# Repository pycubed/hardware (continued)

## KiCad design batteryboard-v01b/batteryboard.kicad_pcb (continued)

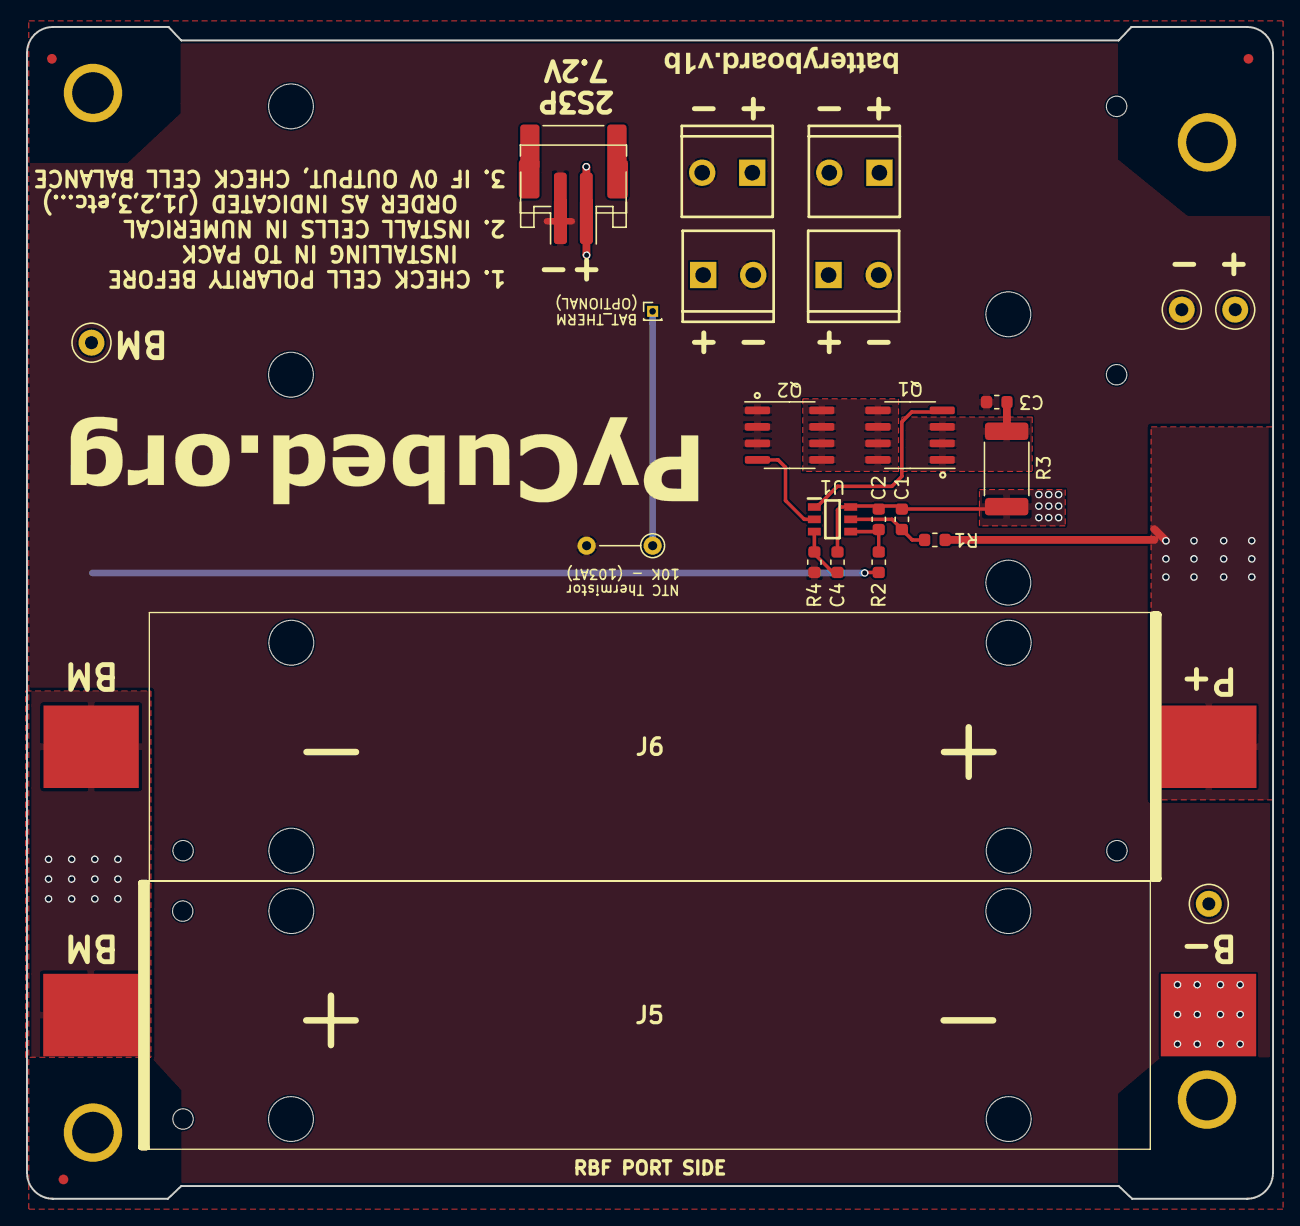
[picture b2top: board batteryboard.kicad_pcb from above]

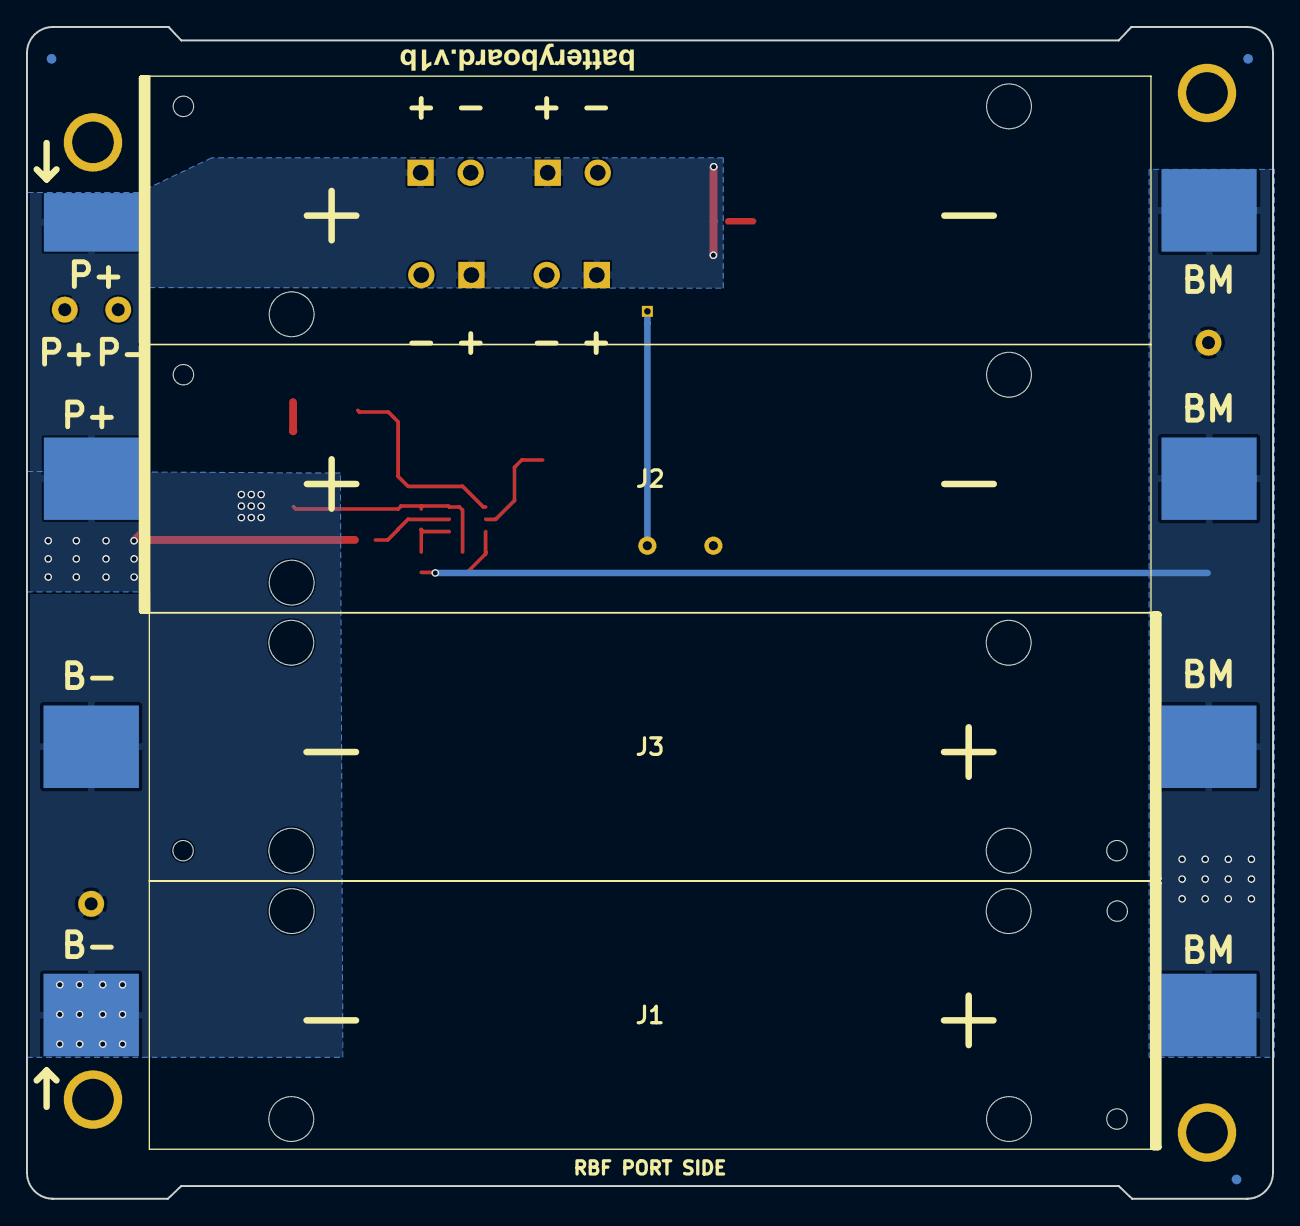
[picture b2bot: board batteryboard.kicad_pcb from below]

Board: 2 copper layers, 95.9 x 90.2 mm, 35 parts (5 on the bottom side), 12 nets.

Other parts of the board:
Ref**: Val**; battery_version
Ref**#2: Val**; battery_version
Ref**#3: Val**; pycubed_logo

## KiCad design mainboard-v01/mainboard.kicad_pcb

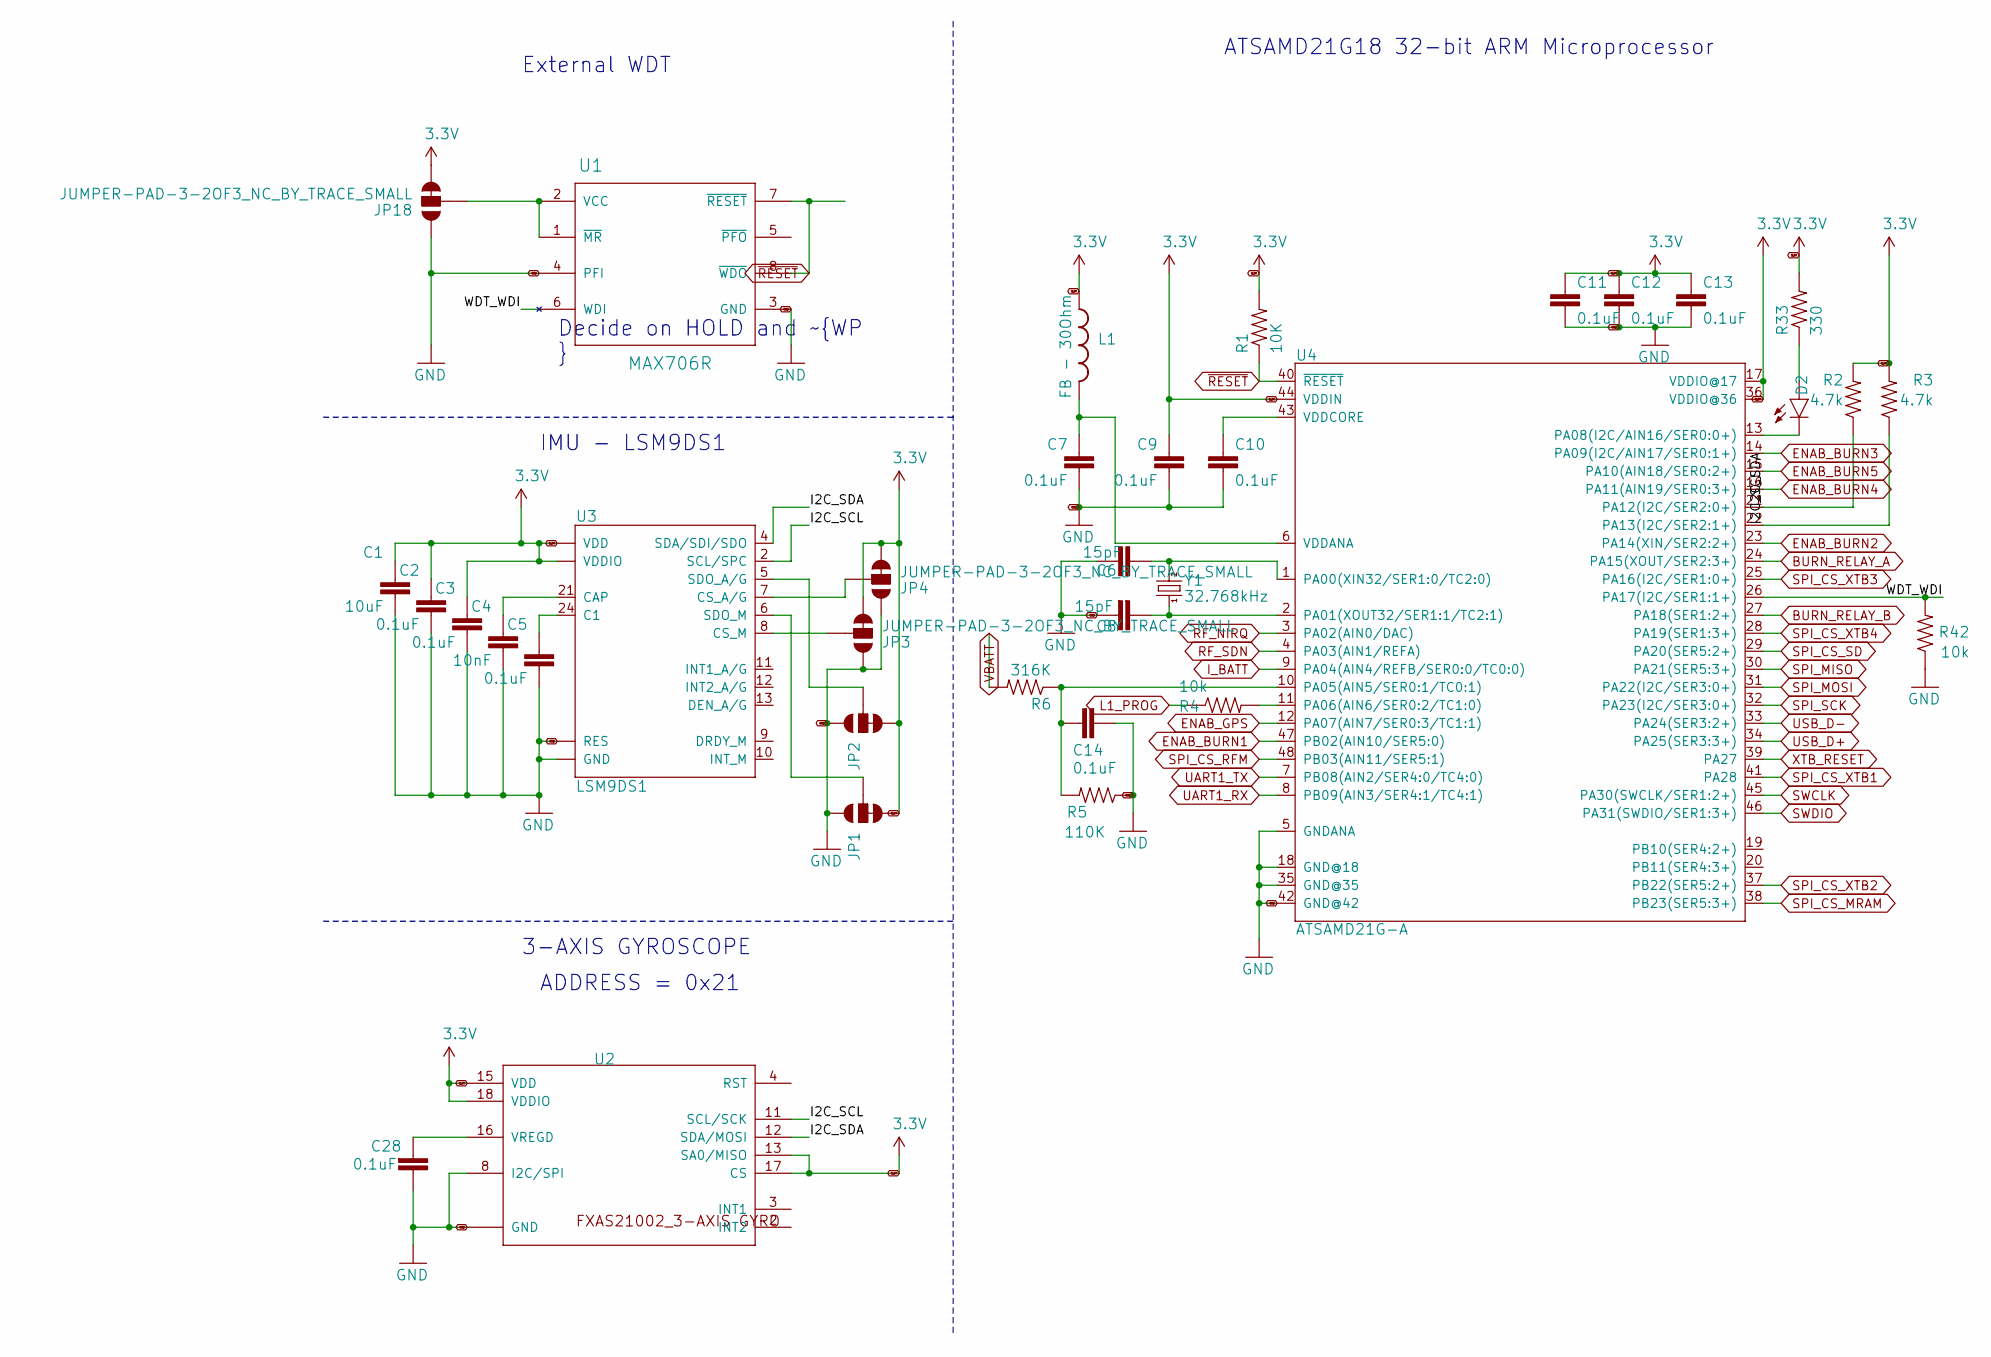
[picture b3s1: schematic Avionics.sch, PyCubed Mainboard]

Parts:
C1: 10uF; C_0603_1608Metric
C2, C3, C5, C7, C9, C10, C11, C12, C13, C14, C28: 0.1uF; C_0603_1608Metric
C4: 10nF; C_0603_1608Metric
C6, C8: 15pF; C_0603_1608Metric
D2: GREEN; LED-0603
JP1, JP2, JP3, JP4, JP18: JUMPER-PAD-3-2OF3_NC_BY_TRACE_SMALL; PAD-JUMPER-3-2OF3_NC_BY_TRACE_YES_SILK_FULL_BOX
L1: FB - 30Ohm; 0603
R1: 10K; R_0603_1608Metric
R2, R3: 4.7k; R_0603_1608Metric
R4, R42: 10k; R_0603_1608Metric
R5: 110K; R_0603_1608Metric
R6: 316K; R_0603_1608Metric
R33: 330; R_0603_1608Metric
U1: MAX706R; SO8
U2: FXAS21002FXAS21002; QFN50P456X400X100-24
U3: LSM9DS1; LGA24-8X4
U4: ATSAMD21G-A; TQFP-48
Y1: 32.768kHz; Crystal_SMD_3215-2Pin_3.2x1.5mm

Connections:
3.3V: C1.1, C2.1, C3.1, C9.1, C11.1, C12.1, C13.1, JP1.3, JP2.3, JP3.3, JP4.3, JP18.3, L1.1, R1.2, R2.2, R3.2, R33.2, U2.13 (SA0/MISO), U2.15 (VDD), U2.17 (CS), U2.18 (VDDIO), U3.1 (VDDIO), U3.3 (VDDIO), U3.22 (VDD), U3.23 (VDD), U4.17 (VDDIO@17), U4.36 (VDDIO@36), U4.44 (VDDIN); also elsewhere on the board
/Avionics/I2C_SCL: R3.1, U2.11 (SCL/SCK), U3.2 (SCL/SPC), U4.22 (PA13(I2C/SER2:1+))
/Avionics/I2C_SDA: R2.1, U2.12 (SDA/MOSI), U3.4 (SDA/SDI/SDO), U4.21 (PA12(I2C/SER2:0+))
/Avionics/WDT_WDI: R42.2, U1.6 (WDI), U4.26 (PA17(I2C/SER1:1+))
BURN_RELAY_A: U4.24 (PA15(XOUT/SER2:3+)); also elsewhere on the board
BURN_RELAY_B: U4.27 (PA18(SER1:2+)); also elsewhere on the board
ENAB_BURN1: U4.47 (PB02(AIN10/SER5:0)); also elsewhere on the board
ENAB_BURN2: U4.23 (PA14(XIN/SER2:2+)); also elsewhere on the board
ENAB_BURN3: U4.14 (PA09(I2C/AIN17/SER0:1+)); also elsewhere on the board
ENAB_BURN4: U4.16 (PA11(AIN19/SER0:3+)); also elsewhere on the board
ENAB_BURN5: U4.15 (PA10(AIN18/SER0:2+)); also elsewhere on the board
ENAB_GPS: U4.12 (PA07(AIN7/SER0:3/TC1:1)); also elsewhere on the board
GND: C1.2, C2.2, C3.2, C4.2, C5.2, C6.1, C7.2, C8.2, C9.2, C10.2, C11.2, C12.2, C13.2, C14.2, C28.1, JP1.1, JP2.1, JP3.1, JP4.1, JP18.1, R5.1, R42.1, U1.3 (GND), U1.4 (PFI), U2.1 (GND), U2.5 (GND), U2.6 (GND), U2.7 (GND), U2.8 (I2C/SPI), U2.9 (GND), U2.10 (GND), U2.14 (GND), U2.19 (GND), U2.20 (GND), U2.21 (GND), U2.22 (GND), U2.23 (GND), U2.24 (GND), U3.14 (RES), U3.15 (RES), U3.16 (RES), U3.17 (RES), U3.18 (RES), U3.19 (GND), U3.20 (GND), U4.5 (GNDANA), U4.18 (GND@18), U4.35 (GND@35), U4.42 (GND@42); also elsewhere on the board
I_BATT: U4.9 (PA04(AIN4/REFB/SER0:0/TC0:0)); also elsewhere on the board
L1_PROG: R4.1; also elsewhere on the board
unnamed: C4.1, U3.21 (CAP)
unnamed: C5.1, U3.24 (C1)
unnamed: C6.2, U4.1 (PA00(XIN32/SER1:0/TC2:0)), Y1.P$2 (2)
unnamed: C7.1, L1.2, U4.6 (VDDANA)
unnamed: C8.1, U4.2 (PA01(XOUT32/SER1:1/TC2:1)), Y1.P$1 (1)
unnamed: C10.1, U4.43 (VDDCORE)
unnamed: C14.1, R5.2, R6.1, U4.10 (PA05(AIN5/SER0:1/TC0:1))
unnamed: C28.2, U2.16 (VREGD)
unnamed: D2.A, R33.1
unnamed: D2.C, U4.13 (PA08(I2C/AIN16/SER0:0+))
unnamed: JP1.2, U3.6 (SDO_M)
unnamed: JP2.2, U3.5 (SDO_A/G)
unnamed: JP3.2, U3.8 (CS_M)
unnamed: JP4.2, U3.7 (CS_A/G)
unnamed: JP18.2, U1.1 (~MR), U1.2 (VCC)
unnamed: R4.2, U4.11 (PA06(AIN6/SER0:2/TC1:0))
RF_NIRQ: U4.3 (PA02(AIN0/DAC)); also elsewhere on the board
RF_SDN: U4.4 (PA03(AIN1/REFA)); also elsewhere on the board
SPI_CS_MRAM: U4.38 (PB23(SER5:3+)); also elsewhere on the board
SPI_CS_RFM: U4.48 (PB03(AIN11/SER5:1)); also elsewhere on the board
SPI_CS_SD: U4.29 (PA20(SER5:2+)); also elsewhere on the board
SPI_CS_XTB1: U4.41 (PA28); also elsewhere on the board
SPI_CS_XTB2: U4.37 (PB22(SER5:2+)); also elsewhere on the board
SPI_CS_XTB3: U4.25 (PA16(I2C/SER1:0+)); also elsewhere on the board
SPI_CS_XTB4: U4.28 (PA19(SER1:3+)); also elsewhere on the board
SPI_MISO: U4.30 (PA21(SER5:3+)); also elsewhere on the board
SPI_MOSI: U4.31 (PA22(I2C/SER3:0+)); also elsewhere on the board
SPI_SCK: U4.32 (PA23(I2C/SER3:0+)); also elsewhere on the board
SWCLK: U4.45 (PA30(SWCLK/SER1:2+)); also elsewhere on the board
SWDIO: U4.46 (PA31(SWDIO/SER1:3+)); also elsewhere on the board
UART1_RX: U4.8 (PB09(AIN3/SER4:1/TC4:1)); also elsewhere on the board
UART1_TX: U4.7 (PB08(AIN2/SER4:0/TC4:0)); also elsewhere on the board
USB_D+: U4.34 (PA25(SER3:3+)); also elsewhere on the board
USB_D-: U4.33 (PA24(SER3:2+)); also elsewhere on the board
VBATT: R6.2; also elsewhere on the board
XTB_RESET: U4.39 (PA27); also elsewhere on the board
~RESET: R1.1, U1.7 (~RESET), U1.8 (~WDO), U4.40 (~RESET~); also elsewhere on the board

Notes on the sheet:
ATSAMD21G18 32-bit ARM Microprocessor
IMU - LSM9DS1
External WDT
Decide on HOLD and ~WP
3-AXIS GYROSCOPE
ADDRESS = 0x21

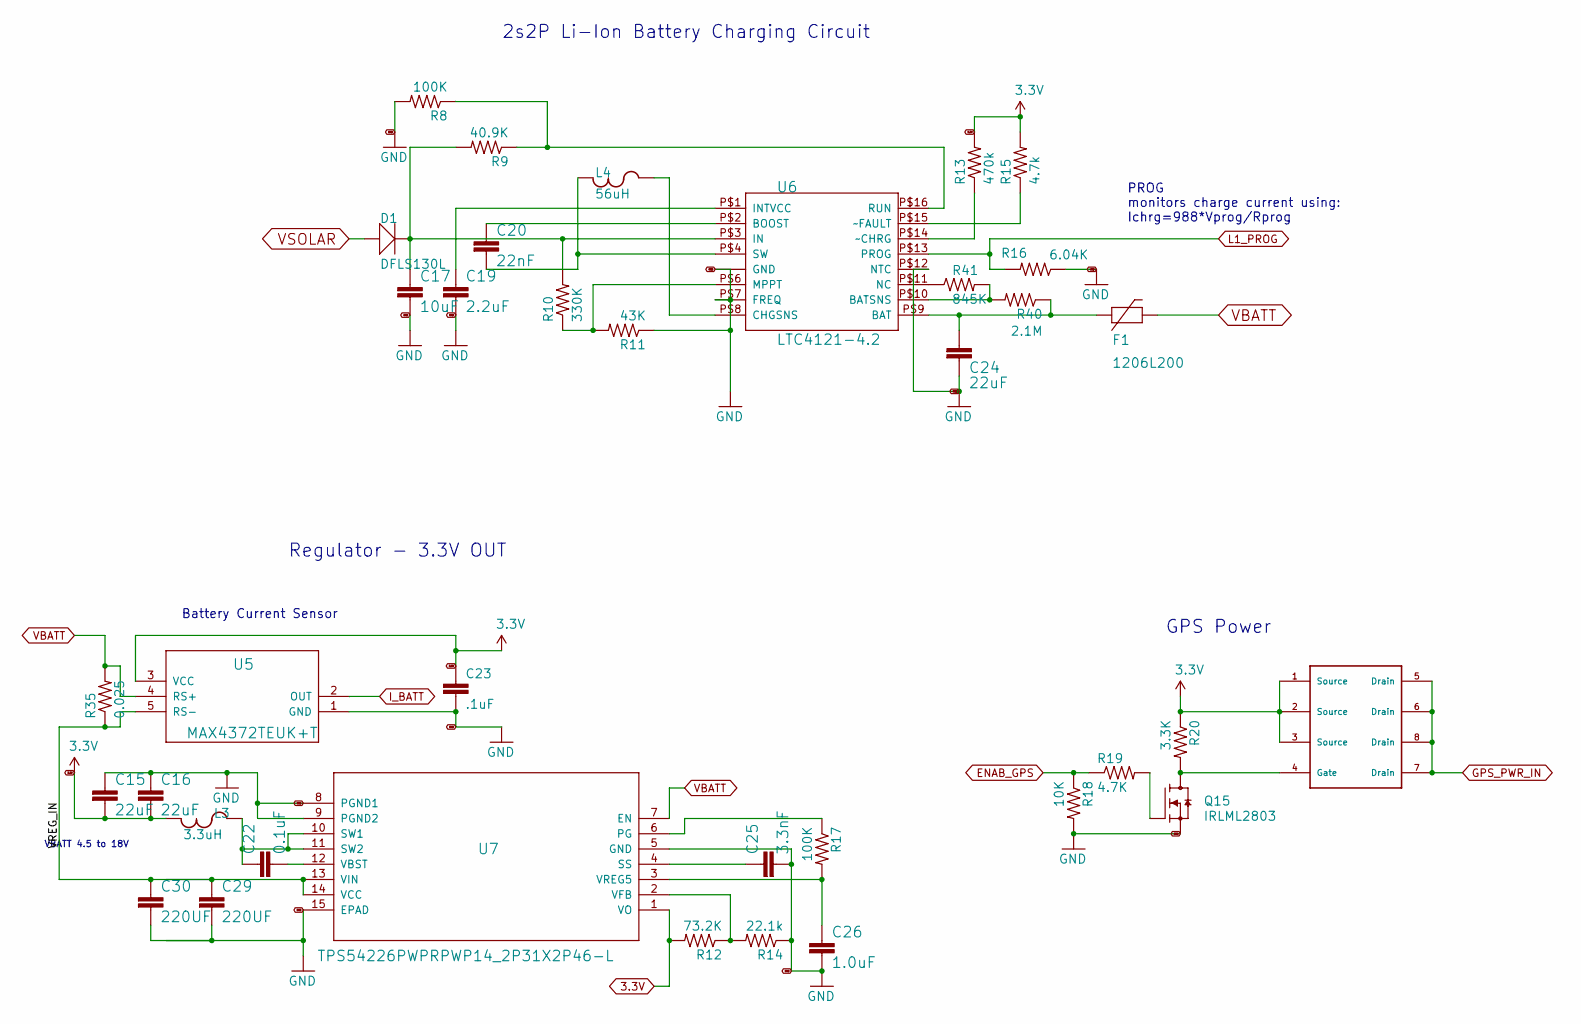
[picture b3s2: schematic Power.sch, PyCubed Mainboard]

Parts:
C15, C16, C24: 22uF; C_0603_1608Metric
C17: 10uF; C_0603_1608Metric
C19: 2.2uF; C_0603_1608Metric
C20: 22nF; C_0603_1608Metric
C22: 0.1uF; C_0603_1608Metric
C23: .1uF; C_0603_1608Metric
C25: 3.3nF; C_0603_1608Metric
C26: 1.0uF; C_0603_1608Metric
C29, C30: 220UF; C_1210_3225Metric
D1: DFLS130L; PWRDI-123
F1: 1206L200; 1206
L3: 3.3uH; 1812
L4: 56uH; 1812
Q15: IRLML2803; SOT-23
R8, R17: 100K; R_0603_1608Metric
R9: 40.9K; R_0603_1608Metric
R10: 330K; R_0603_1608Metric
R11: 43K; R_0603_1608Metric
R12: 73.2K; R_0603_1608Metric
R13: 470k; R_0603_1608Metric
R14: 22.1k; R_0603_1608Metric
R15: 4.7k; R_0603_1608Metric
R16: 6.04K; R_0603_1608Metric
R18: 10K; R_0603_1608Metric
R19: 4.7K; R_0603_1608Metric
R20: 3.3K; R_0603_1608Metric
R35: 0.025; R_2512_6332Metric
R40: 2.1M; R_0603_1608Metric
R41: 845K; R_0603_1608Metric
U5: MAX4372TEUK+T; 21-0057F
U6: LTC4121-4.2; QFN-16-PAD
U7: TPS54226PWPRPWP14_2P31X2P46-L; PWP14_2P31X2P46-L
U11: NDS8434

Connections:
3.3V: C15.2, C16.2, C23.1, L3.P$1, R12.2, R13.2, R15.2, R20.1, U5.3 (VCC), U7.1 (VO), U11.1 (Source), U11.2 (Source), U11.3 (Source); also elsewhere on the board
/Power/VREG_IN: C29.1, C30.1, R35.1, U5.5 (RS-), U7.13 (VIN), U7.14 (VCC)
ENAB_GPS: R18.1, R19.1; also elsewhere on the board
GND: C15.1, C16.1, C17.2, C19.2, C23.2, C24.2, C25.2, C26.2, C29.2, C30.2, Q15.2 (S), R8.2, R11.1, R14.1, R16.1, R18.2, U5.1 (GND), U6.P$5 (GND), U6.P$7 (FREQ), U6.P$12 (NTC), U6.P$17 (GND), U7.5 (GND), U7.8 (PGND1), U7.9 (PGND2), U7.15 (EPAD); also elsewhere on the board
I_BATT: U5.2 (OUT); also elsewhere on the board
L1_PROG: R16.2, U6.P$13 (PROG); also elsewhere on the board
unnamed: C17.1, D1.C, R9.2, R10.2, U6.P$3 (IN)
unnamed: C19.1, U6.P$1 (INTVCC)
unnamed: C20.1, U6.P$2 (BOOST)
unnamed: C20.2, L4.P$1, U6.P$4 (SW)
unnamed: C22.1, L3.P$2, U7.10 (SW1), U7.11 (SW2)
unnamed: C22.2, U7.12 (VBST)
unnamed: C24.1, F1.1, R40.1, U6.P$9 (BAT)
unnamed: C25.1, U7.4 (SS)
unnamed: C26.1, R17.2, U7.3 (VREG5)
unnamed: L4.P$2, U6.P$8 (CHGSNS)
unnamed: Q15.1 (G), R19.2
unnamed 82: Q15.3 (D), R20.2, U11.4 (Gate); also elsewhere on the board
unnamed: R8.1, R9.1, U6.P$16 (RUN)
unnamed: R10.1, R11.2, U6.P$6 (MPPT)
unnamed: R12.1, R14.2, U7.2 (VFB)
unnamed: R13.1, U6.P$14 (~~CHRG)
unnamed: R15.1, U6.P$15 (~~FAULT)
unnamed: R17.1, U7.6 (PG)
unnamed: R40.2, R41.2, U6.P$10 (BATSNS)
unnamed: R41.1, U6.P$11 (NC)
unnamed: U11.5 (Drain), U11.6 (Drain), U11.7 (Drain), U11.8 (Drain)
VBATT: F1.2, R35.2, U5.4 (RS+), U7.7 (EN); also elsewhere on the board
VSOLAR: D1.A; also elsewhere on the board

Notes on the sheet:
Battery Current Sensor
GPS Power
2s2P Li-Ion Battery Charging Circuit
Regulator - 3.3V OUT
VBATT 4.5 to 18V
PROG monitors charge current using: Ichrg=988*Vprog/Rprog

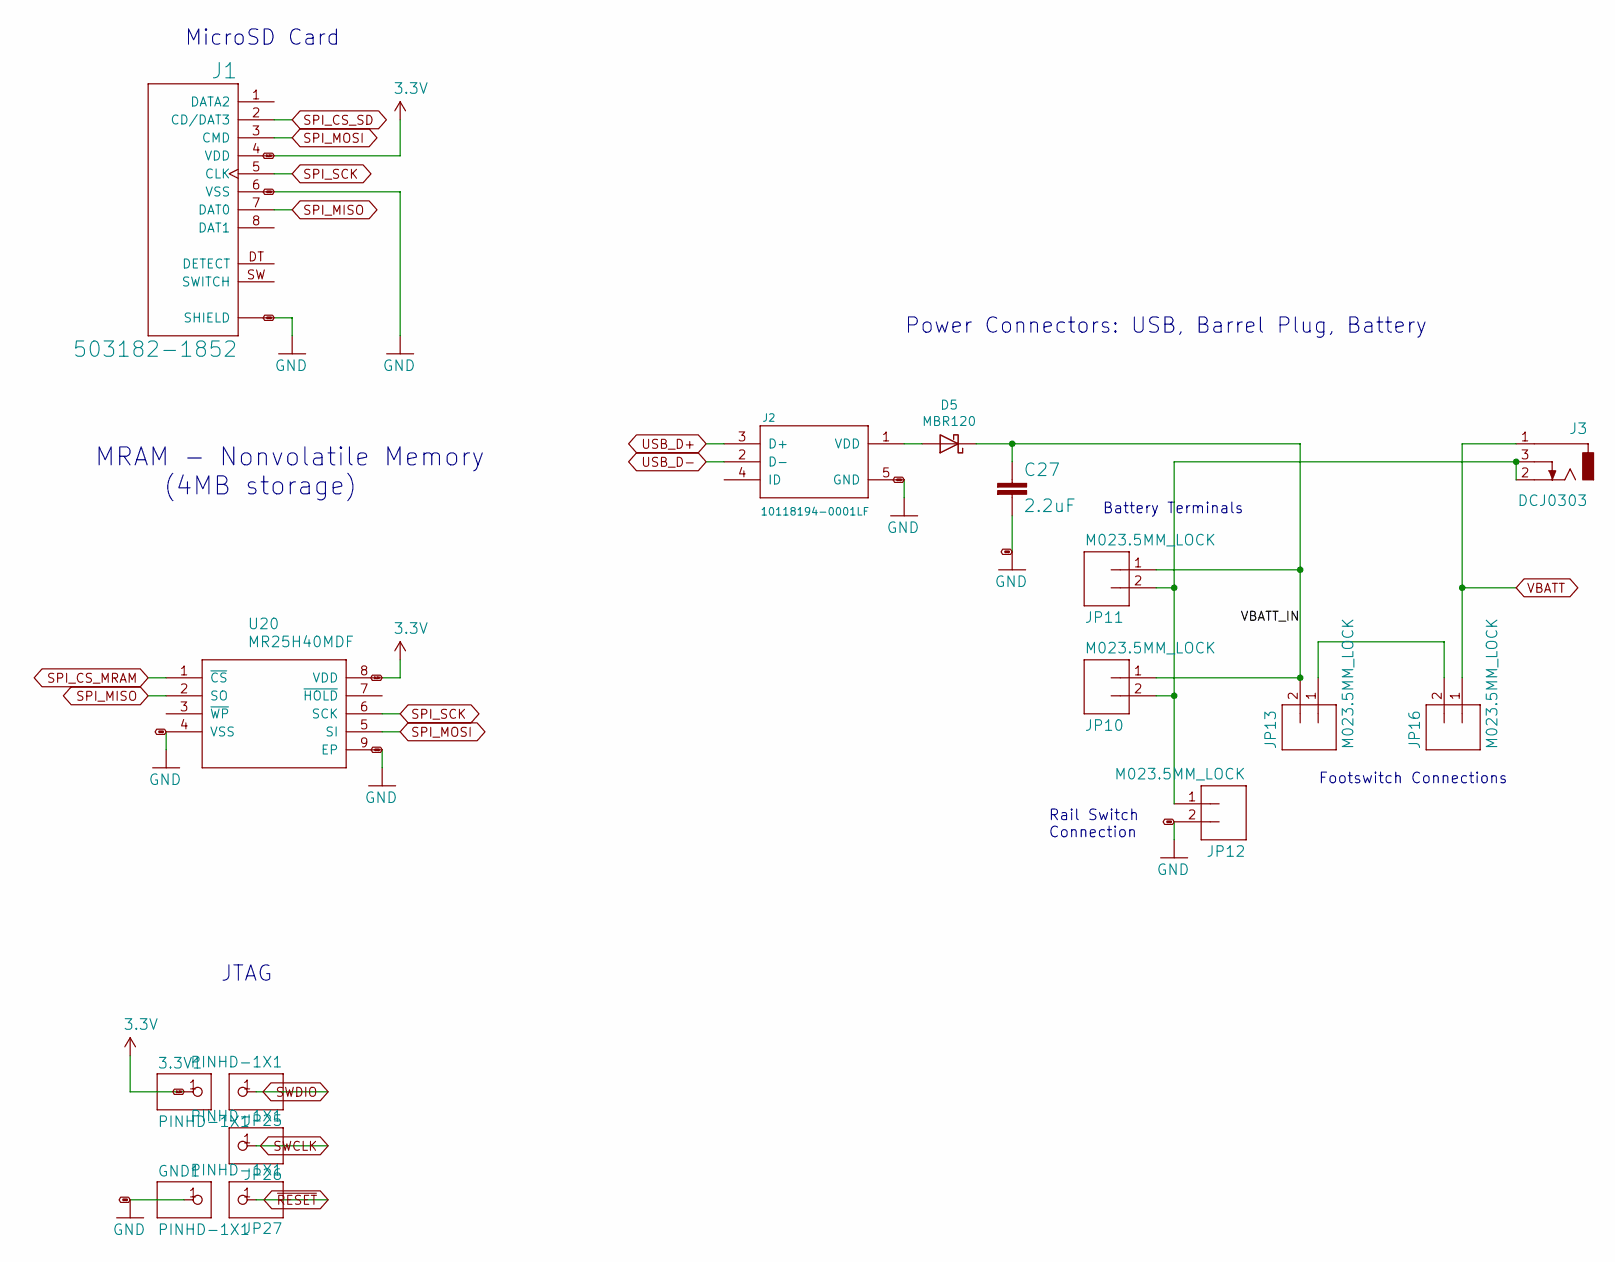
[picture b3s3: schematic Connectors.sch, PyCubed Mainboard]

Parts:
3.3V: PINHD-1X1; 1X01
C27: 2.2uF; C_0603_1608Metric
D5: MBR120; D_SOD-123
GND: PINHD-1X1; 1X01
J1: 503182-1852; MOLEX_503182-1852
J2: 10118194-0001LF; FRAMATOME_10118194-0001LF
J3: DCJ0303
JP10, JP11, JP12, JP13, JP16: M023.5MM_LOCK; SCREWTERMINAL-3.5MM-2_LOCK
JP25, JP26, JP27: PINHD-1X1; 1X01
U20: MR25H40MDF; SON127P600X500X90-9N

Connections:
3.3V: J1.4 (VDD), U20.8 (VDD); also elsewhere on the board
/Connectors/VBATT_IN: C27.1, D5.1 (K), JP10.1, JP11.1, JP13.2; also elsewhere on the board
GND: C27.2, J1.6 (VSS), J1.P1 (SHIELD), J1.P2 (SHIELD), J1.P3 (SHIELD), J1.P4 (SHIELD), J1.P5 (SHIELD), J2.5 (GND), JP12.2, U20.4 (VSS), U20.9 (EP); also elsewhere on the board
unnamed: D5.2 (A), J2.1 (VDD)
unnamed: J3.2, J3.3, JP10.2, JP11.2, JP12.1
unnamed: JP13.1, JP16.2
SPI_CS_MRAM: U20.1 (~CS); also elsewhere on the board
SPI_CS_SD: J1.2 (CD/DAT3); also elsewhere on the board
SPI_MISO: J1.7 (DAT0), U20.2 (SO); also elsewhere on the board
SPI_MOSI: J1.3 (CMD), U20.5 (SI); also elsewhere on the board
SPI_SCK: J1.5 (CLK), U20.6 (SCK); also elsewhere on the board
SWCLK: JP26.1; also elsewhere on the board
SWDIO: JP25.1; also elsewhere on the board
USB_D+: J2.3 (D+); also elsewhere on the board
USB_D-: J2.2 (D-); also elsewhere on the board
VBATT: J3.1, JP16.1; also elsewhere on the board
~RESET: JP27.1; also elsewhere on the board

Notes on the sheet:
Footswitch Connections
Battery Terminals
Rail Switch Connection
JTAG
Power Connectors: USB, Barrel Plug, Battery
MicroSD Card
MRAM - Nonvolatile Memory (4MB storage)

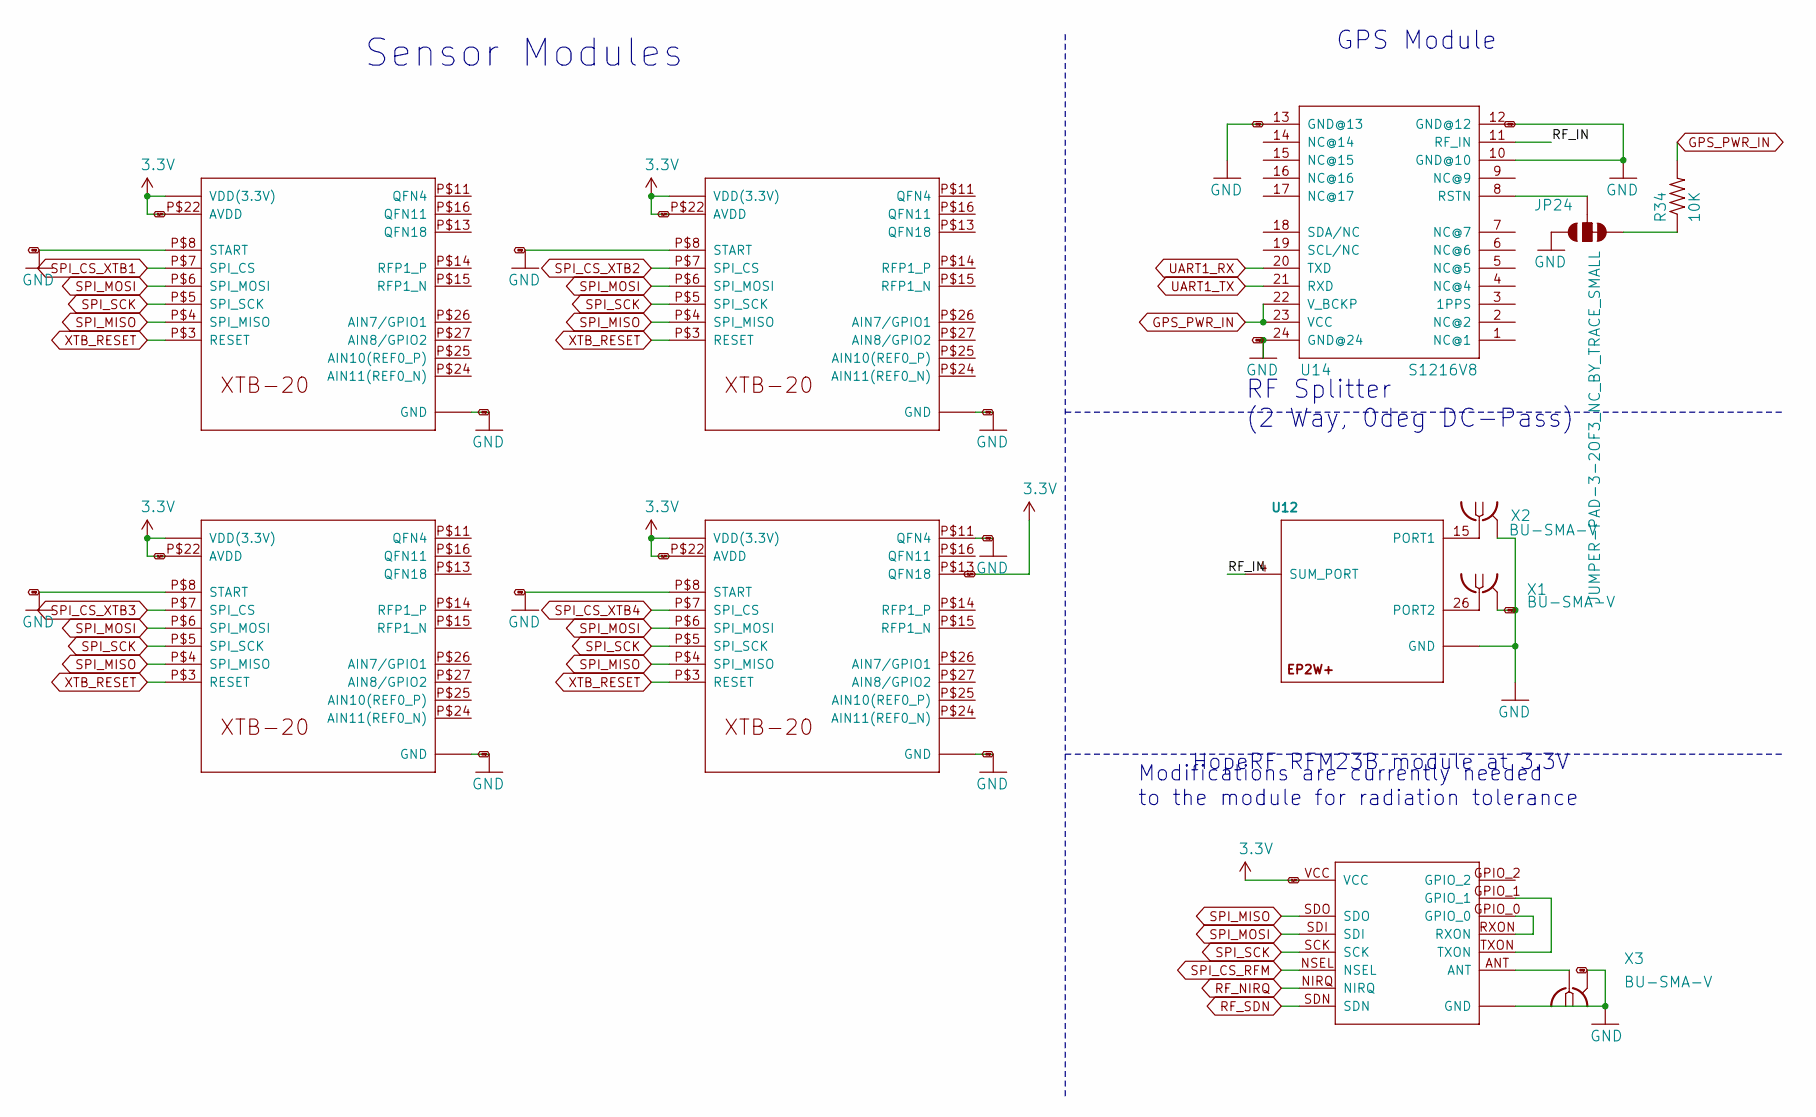
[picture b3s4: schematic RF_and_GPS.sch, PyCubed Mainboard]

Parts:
JP24: JUMPER-PAD-3-2OF3_NC_BY_TRACE_SMALL; PAD-JUMPER-3-2OF3_NC_BY_TRACE_YES_SILK_FULL_BOX
R34: 10K; R_0603_1608Metric
U12: EP2W+; QFN32-5X5MM
U13: RFM23BP
U14: S1216V8; S1216_24PIN_PACKAGE
U15, U16, U17, U18: XTB_2018_07_15; XTB28_MEZ
X1, X2, X3: BU-SMA-V; SMA_Amphenol_132134-16_Vertical

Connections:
3.3V: U13.VCC, U15.P$1 (VDD(3.3V)), U15.P$20 (VDD(3.3V)), U15.P$22 (AVDD), U15.P$28 (VDD(3.3V)), U16.P$1 (VDD(3.3V)), U16.P$20 (VDD(3.3V)), U16.P$22 (AVDD), U16.P$28 (VDD(3.3V)), U17.P$1 (VDD(3.3V)), U17.P$20 (VDD(3.3V)), U17.P$22 (AVDD), U17.P$28 (VDD(3.3V)), U18.P$1 (VDD(3.3V)), U18.P$13 (QFN18), U18.P$20 (VDD(3.3V)), U18.P$22 (AVDD), U18.P$28 (VDD(3.3V)); also elsewhere on the board
/RF and GPS/RF_IN: U12.4 (SUM_PORT), U14.11 (RF_IN)
GND: JP24.1, U12.1 (GND), U12.2 (GND), U12.3 (GND), U12.5 (GND), U12.6 (GND), U12.7 (GND), U12.8 (GND), U12.9 (GND), U12.10 (GND), U12.11 (GND), U12.12 (GND), U12.13 (GND), U12.14 (GND), U12.16 (GND), U12.17 (GND), U12.18 (GND), U12.19 (GND), U12.20 (GND), U12.21 (GND), U12.22 (GND), U12.23 (GND), U12.24 (GND), U12.25 (GND), U12.27 (GND), U12.28 (GND), U12.29 (GND), U12.30 (GND), U12.31 (GND), U12.32 (GND), U12.EP (GND), U13.GND1 (GND), U13.GND2 (GND), U13.GND3 (GND), U14.10 (GND@10), U14.12 (GND@12), U14.13 (GND@13), U14.24 (GND@24), U15.P$2 (GND), U15.P$8 (START), U15.P$9 (GND), U15.P$10 (GND), U15.P$12 (GND), U15.P$17 (GND), U15.P$19 (GND), U15.P$21 (GND), U15.P$23 (GND), U16.P$2 (GND), U16.P$8 (START), U16.P$9 (GND), U16.P$10 (GND), U16.P$12 (GND), U16.P$17 (GND), U16.P$19 (GND), U16.P$21 (GND), U16.P$23 (GND), U17.P$2 (GND), U17.P$8 (START), U17.P$9 (GND), U17.P$10 (GND), U17.P$12 (GND), U17.P$17 (GND), U17.P$19 (GND), U17.P$21 (GND), U17.P$23 (GND), U18.P$2 (GND), U18.P$8 (START), U18.P$9 (GND), U18.P$10 (GND), U18.P$11 (QFN4), U18.P$12 (GND), U18.P$17 (GND), U18.P$19 (GND), U18.P$21 (GND), U18.P$23 (GND), X1.2, X1.3 (2), X1.4 (2), X1.5 (2), X2.2, X2.3 (2), X2.4 (2), X2.5 (2), X3.2, X3.3 (2), X3.4 (2), X3.5 (2); also elsewhere on the board
GPS_PWR_IN: R34.2, U14.22 (V_BCKP), U14.23 (VCC); also elsewhere on the board
unnamed: JP24.2, U14.8 (RSTN)
unnamed: JP24.3, R34.1
unnamed: U12.15 (PORT1), X2.1
unnamed: U12.26 (PORT2), X1.1
unnamed: U13.ANT, X3.1
unnamed: U13.GPIO_0, U13.RXON
unnamed: U13.GPIO_1, U13.TXON
RF_NIRQ: U13.NIRQ; also elsewhere on the board
RF_SDN: U13.SDN; also elsewhere on the board
SPI_CS_RFM: U13.NSEL; also elsewhere on the board
SPI_CS_XTB1: U15.P$7 (SPI_CS); also elsewhere on the board
SPI_CS_XTB2: U16.P$7 (SPI_CS); also elsewhere on the board
SPI_CS_XTB3: U17.P$7 (SPI_CS); also elsewhere on the board
SPI_CS_XTB4: U18.P$7 (SPI_CS); also elsewhere on the board
SPI_MISO: U13.SDO, U15.P$4 (SPI_MISO), U16.P$4 (SPI_MISO), U17.P$4 (SPI_MISO), U18.P$4 (SPI_MISO); also elsewhere on the board
SPI_MOSI: U13.SDI, U15.P$6 (SPI_MOSI), U16.P$6 (SPI_MOSI), U17.P$6 (SPI_MOSI), U18.P$6 (SPI_MOSI); also elsewhere on the board
SPI_SCK: U13.SCK, U15.P$5 (SPI_SCK), U16.P$5 (SPI_SCK), U17.P$5 (SPI_SCK), U18.P$5 (SPI_SCK); also elsewhere on the board
UART1_RX: U14.20 (TXD); also elsewhere on the board
UART1_TX: U14.21 (RXD); also elsewhere on the board
XTB_RESET: U15.P$3 (RESET), U16.P$3 (RESET), U17.P$3 (RESET), U18.P$3 (RESET); also elsewhere on the board

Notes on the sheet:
GPS Module
HopeRF RFM23B module at 3.3V
Modifications are currently needed to the module for radiation tolerance
RF Splitter (2 Way, 0deg DC-Pass)
Sensor Modules

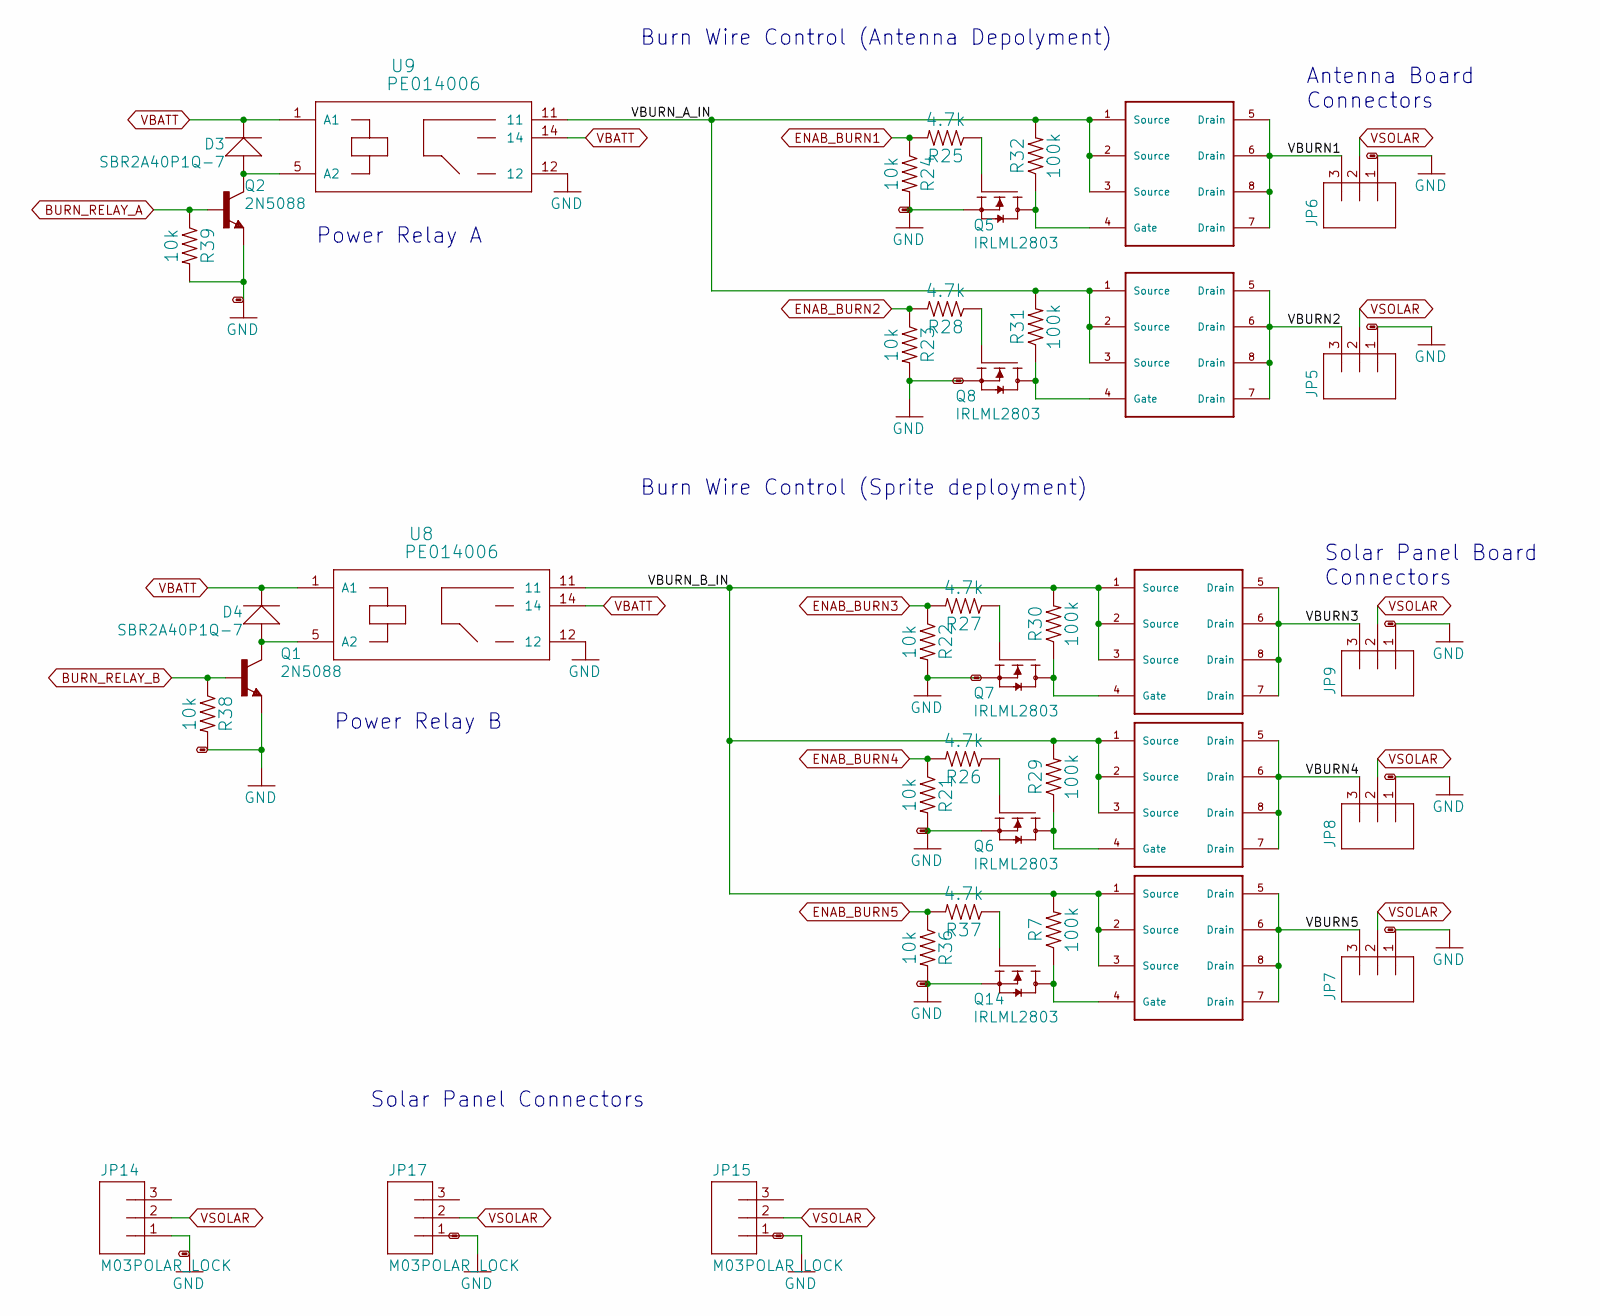
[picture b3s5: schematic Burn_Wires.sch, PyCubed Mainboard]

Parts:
D3, D4: SBR2A40P1Q-7; PWRDI-123
JP5, JP6, JP7, JP8, JP9, JP14, JP15, JP17: M03POLAR_LOCK; MOLEX-1X3_LOCK
Q1, Q2: 2N5088; SOT23
Q5, Q6, Q7, Q8, Q14: IRLML2803; SOT-23
R7, R29, R30, R31, R32: 100k; R_0603_1608Metric
R21, R22, R23, R24, R36, R38, R39: 10k; R_0603_1608Metric
R25, R26, R27, R28, R37: 4.7k; R_0603_1608Metric
U8, U9: PE014006; RELAY5-PE_CO
U19, U21, U22, U23, U24: NDS8434

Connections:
/Burn Wires/VBURN1: JP6.3, U19.5 (Drain), U19.6 (Drain), U19.7 (Drain), U19.8 (Drain); also elsewhere on the board
/Burn Wires/VBURN2: JP5.3, U21.5 (Drain), U21.6 (Drain), U21.7 (Drain), U21.8 (Drain); also elsewhere on the board
/Burn Wires/VBURN3: JP9.3, U22.5 (Drain), U22.6 (Drain), U22.7 (Drain), U22.8 (Drain); also elsewhere on the board
/Burn Wires/VBURN4: JP8.3, U23.5 (Drain), U23.6 (Drain), U23.7 (Drain), U23.8 (Drain); also elsewhere on the board
/Burn Wires/VBURN5: JP7.3, U24.5 (Drain), U24.6 (Drain), U24.7 (Drain), U24.8 (Drain); also elsewhere on the board
/Burn Wires/VBURN_A_IN: R31.2, R32.2, U9.11, U19.1 (Source), U19.2 (Source), U19.3 (Source), U21.1 (Source), U21.2 (Source), U21.3 (Source); also elsewhere on the board
/Burn Wires/VBURN_B_IN: R7.2, R29.2, R30.2, U8.11, U22.1 (Source), U22.2 (Source), U22.3 (Source), U23.1 (Source), U23.2 (Source), U23.3 (Source), U24.1 (Source), U24.2 (Source), U24.3 (Source); also elsewhere on the board
BURN_RELAY_A: Q2.1 (B), R39.1; also elsewhere on the board
BURN_RELAY_B: Q1.1 (B), R38.1; also elsewhere on the board
ENAB_BURN1: R24.1, R25.2; also elsewhere on the board
ENAB_BURN2: R23.1, R28.2; also elsewhere on the board
ENAB_BURN3: R22.1, R27.2; also elsewhere on the board
ENAB_BURN4: R21.1, R26.2; also elsewhere on the board
ENAB_BURN5: R36.1, R37.2; also elsewhere on the board
GND: JP5.1, JP6.1, JP7.1, JP8.1, JP9.1, JP14.1, JP15.1, JP17.1, Q1.2 (E), Q2.2 (E), Q5.2 (S), Q6.2 (S), Q7.2 (S), Q8.2 (S), Q14.2 (S), R21.2, R22.2, R23.2, R24.2, R36.2, R38.2, R39.2, U8.12, U9.12; also elsewhere on the board
unnamed: D3.A, Q2.3 (C), U9.5 (A2)
unnamed: D4.A, Q1.3 (C), U8.5 (A2)
unnamed: Q5.1 (G), R25.1
unnamed: Q5.3 (D), R32.1, U19.4 (Gate)
unnamed: Q6.1 (G), R26.1
unnamed: Q6.3 (D), R29.1, U23.4 (Gate)
unnamed: Q7.1 (G), R27.1
unnamed: Q7.3 (D), R30.1, U22.4 (Gate)
unnamed: Q8.1 (G), R28.1
unnamed: Q8.3 (D), R31.1, U21.4 (Gate)
unnamed: Q14.1 (G), R37.1
unnamed: Q14.3 (D), R7.1, U24.4 (Gate)
VBATT: D3.C, D4.C, U8.1 (A1), U8.14, U9.1 (A1), U9.14; also elsewhere on the board
VSOLAR: JP5.2, JP6.2, JP7.2, JP8.2, JP9.2, JP14.2, JP15.2, JP17.2; also elsewhere on the board

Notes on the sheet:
Power Relay A
Burn Wire Control (Antenna Depolyment)
Burn Wire Control (Sprite deployment)
Power Relay B
Antenna Board Connectors
Solar Panel Board Connectors
Solar Panel Connectors
